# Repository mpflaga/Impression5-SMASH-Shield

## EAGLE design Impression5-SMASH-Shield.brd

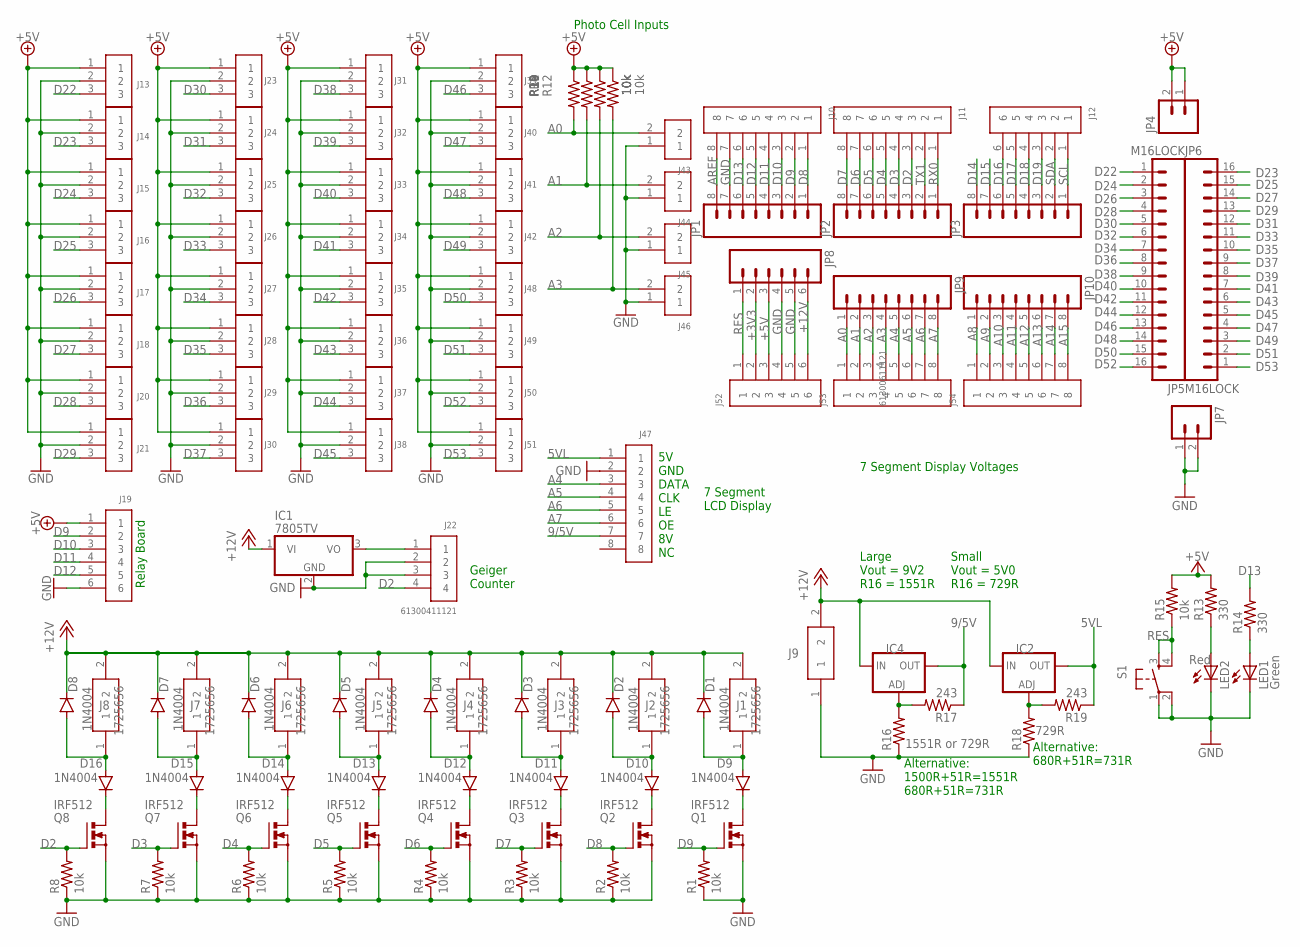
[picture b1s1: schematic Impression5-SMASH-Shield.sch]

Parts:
D1, D2, D3, D4, D5, D6, D7, D8, D9, D10, D11, D12, D13, D14, D15, D16: 1N4004; DO41-10
IC1: 7805TV; TO220V
IC2, IC4: LM317TS; 317TS
J1, J2, J3, J4, J5, J6, J7, J8, J9: 1725656
J10, J11, J47, J53, J54: 61300811121
J12, J19, J52: 61300611121
J13, J14, J15, J16, J17, J18, J20, J21, J23, J24, J25, J26, J27, J28, J29, J30, J31, J32, J33, J34, J35, J36, J37, J38, J39, J40, J41, J42, J48, J49, J50, J51: 61300311121
J22: 61300411121
J43, J44, J45, J46: 61300211121
JP1, JP2, JP3, JP9, JP10: M08LOCK; 1X08_LOCK
JP4, JP7: M02LOCK; 1X02_LOCK
JP5, JP6: M16LOCK; 1X16_LOCK
JP8: M06LOCK; 1X06_LOCK
LED1: Green; LED5MM
LED2: Red; LED5MM
Q1, Q2, Q3, Q4, Q5, Q6, Q7, Q8: IRF512; TO220BV
R1, R2, R3, R4, R5, R6, R7, R8, R9, R10, R11, R12, R15: 10k; AXIAL-0.3
R13, R14: 330; AXIAL-0.3
R16: 1551R or 729R; AXIAL-0.3
R17, R19: 243; AXIAL-0.3
R18: 729R; AXIAL-0.3
S1: TAC_SWITCHPTH; TACTILE-PTH

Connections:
5VG: IC1.3 (VO), J22.1
5VL: IC2.2 (OUT), J47.1, R19.P$1 (1)
9/5V: IC4.2 (OUT), J47.7, R17.P$1 (1)
+3V3: J52.2, JP8.2
+5V: J13.1, J14.1, J15.1, J16.1, J17.1, J18.1, J19.1, J20.1, J21.1, J23.1, J24.1, J25.1, J26.1, J27.1, J28.1, J29.1, J30.1, J31.1, J32.1, J33.1, J34.1, J35.1, J36.1, J37.1, J38.1, J39.1, J40.1, J41.1, J42.1, J48.1, J49.1, J50.1, J51.1, J52.3, JP4.1, JP4.2, JP8.3, R9.P$1 (1), R10.P$1 (1), R11.P$1 (1), R12.P$1 (1), R13.P$2 (2), R15.P$2 (2)
+12V: D1.C, D2.C, D3.C, D4.C, D5.C, D6.C, D7.C, D8.C, IC1.1 (VI), IC2.3 (IN), IC4.3 (IN), J1.2, J2.2, J3.2, J4.2, J5.2, J6.2, J7.2, J8.2, J9.2, J52.6, JP8.6
A0: J43.2, J53.1, JP9.1, R9.P$2 (2)
A1: J44.2, J53.2, JP9.2, R10.P$2 (2)
A2: J45.2, J53.3, JP9.3, R11.P$2 (2)
A3: J46.2, J53.4, JP9.4, R12.P$2 (2)
A4: J47.3, J53.5, JP9.5
A5: J47.4, J53.6, JP9.6
A6: J47.5, J53.7, JP9.7
A7: J47.6, J53.8, JP9.8
A8: J54.1, JP10.1
A9: J54.2, JP10.2
A10: J54.3, JP10.3
A11: J54.4, JP10.4
A12: J54.5, JP10.5
A13: J54.6, JP10.6
A14: J54.7, JP10.7
A15: J54.8, JP10.8
AREF: J10.8, JP1.8
D2: J11.3, J22.4, JP2.3, Q8.G, R8.P$2 (2)
D3: J11.4, JP2.4, Q7.G, R7.P$2 (2)
D4: J11.5, JP2.5, Q6.G, R6.P$2 (2)
D5: J11.6, JP2.6, Q5.G, R5.P$2 (2)
D6: J11.7, JP2.7, Q4.G, R4.P$2 (2)
D7: J11.8, JP2.8, Q3.G, R3.P$2 (2)
D8: J10.1, JP1.1, Q2.G, R2.P$2 (2)
D9: J10.2, J19.2, JP1.2, Q1.G, R1.P$2 (2)
D10: J10.3, J19.3, JP1.3
D11: J10.4, J19.4, JP1.4
D12: J10.5, J19.5, JP1.5
D13: J10.6, JP1.6, R14.P$2 (2)
D14: JP3.8
D15: JP3.7
D16: J12.6, JP3.6
D17: J12.5, JP3.5
D18: J12.4, JP3.4
D19: J12.3, JP3.3
D22: J13.3, JP5.1
D23: J14.3, JP6.16
D24: J15.3, JP5.2
D25: J16.3, JP6.15
D26: J17.3, JP5.3
D27: J18.3, JP6.14
D28: J20.3, JP5.4
D29: J21.3, JP6.13
D30: J23.3, JP5.5
D31: J24.3, JP6.12
D32: J25.3, JP5.6
D33: J26.3, JP6.11
D34: J27.3, JP5.7
D35: J28.3, JP6.10
D36: J29.3, JP5.8
D37: J30.3, JP6.9
D38: J31.3, JP5.9
D39: J32.3, JP6.8
D40: J33.3, JP5.10
D41: J34.3, JP6.7
D42: J35.3, JP5.11
D43: J36.3, JP6.6
D44: J37.3, JP5.12
D45: J38.3, JP6.5
D46: J39.3, JP5.13
D47: J40.3, JP6.4
D48: J41.3, JP5.14
D49: J42.3, JP6.3
D50: J48.3, JP5.15
D51: J49.3, JP6.2
D52: J50.3, JP5.16
D53: J51.3, JP6.1
GND: IC1.2 (GND), J9.1, J10.7, J13.2, J14.2, J15.2, J16.2, J17.2, J18.2, J19.6, J20.2, J21.2, J22.2, J22.3, J23.2, J24.2, J25.2, J26.2, J27.2, J28.2, J29.2, J30.2, J31.2, J32.2, J33.2, J34.2, J35.2, J36.2, J37.2, J38.2, J39.2, J40.2, J41.2, J42.2, J43.1, J44.1, J45.1, J46.1, J47.2, J48.2, J49.2, J50.2, J51.2, J52.4, J52.5, JP1.7, JP7.1, JP7.2, JP8.4, JP8.5, LED1.K (C), LED2.K (C), Q1.S, Q2.S, Q3.S, Q4.S, Q5.S, Q6.S, Q7.S, Q8.S, R1.P$1 (1), R2.P$1 (1), R3.P$1 (1), R4.P$1 (1), R5.P$1 (1), R6.P$1 (1), R7.P$1 (1), R8.P$1 (1), R16.P$1 (1), R18.P$1 (1), S1.1, S1.2
unnamed: D8.A, D16.A, J8.1
unnamed: D16.C, Q8.D
unnamed: D7.A, D15.A, J7.1
unnamed: D15.C, Q7.D
unnamed: D6.A, D14.A, J6.1
unnamed: D14.C, Q6.D
unnamed: D5.A, D13.A, J5.1
unnamed: D13.C, Q5.D
unnamed: D4.A, D12.A, J4.1
unnamed: D12.C, Q4.D
unnamed: D3.A, D11.A, J3.1
unnamed: D11.C, Q3.D
unnamed: D2.A, D10.A, J2.1
unnamed: D10.C, Q2.D
unnamed: D1.A, D9.A, J1.1
unnamed: D9.C, Q1.D
unnamed: IC4.1 (ADJ), R16.P$2 (2), R17.P$2 (2)
unnamed: IC2.1 (ADJ), R18.P$2 (2), R19.P$2 (2)
unnamed: LED2.A, R13.P$1 (1)
unnamed: LED1.A, R14.P$1 (1)
RES: J52.1, JP8.1, R15.P$1 (1), S1.3, S1.4
RX0: J11.1, JP2.1
SCL: J12.1, JP3.1
SDA: J12.2, JP3.2
TX1: J11.2, JP2.2

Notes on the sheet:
Relay Board
Photo Cell Inputs
5V GND DATA CLK LE OE 8V NC
7 Segment LCD Display
Geiger Counter
7 Segment Display Voltages
Large Vout = 9V2 R16 = 1551R
Small Vout = 5V0 R16 = 729R
Alternative: 680R+51R=731R
Alternative: 1500R+51R=1551R 680R+51R=731R

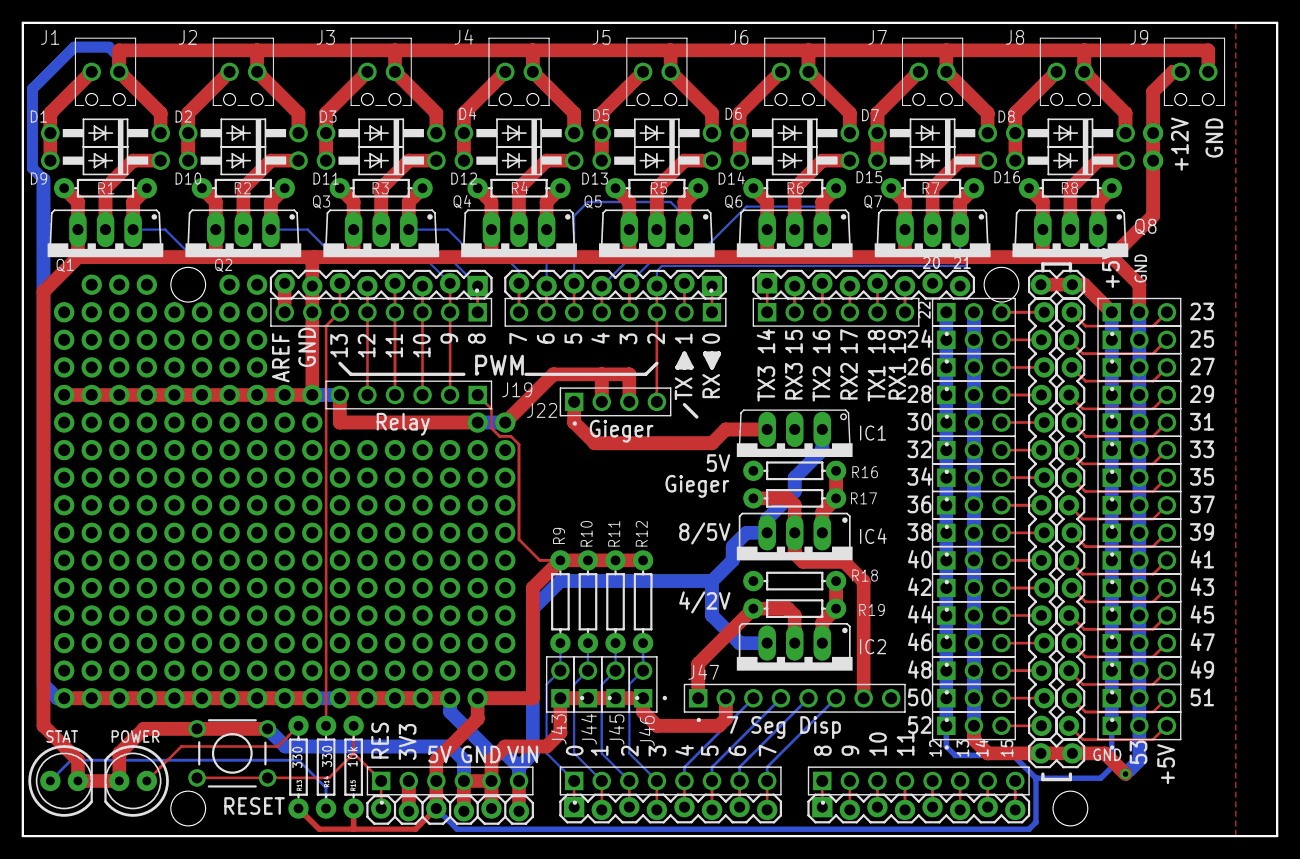
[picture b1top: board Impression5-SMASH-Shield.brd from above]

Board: 2 copper layers, 115.6 x 74.9 mm, 113 parts (0 on the bottom side), 97 nets.

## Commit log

2019-08-04 Changed the Order of the Text to better line up the LM317 Programming Resistors.
2019-08-04 changed 4/2V to 5VL. This powers the VDD of the TLC5917 and needs to be 5V.
2019-08-04 Changed the 8/5V to 9/5V, actually 9V2 and 5V0 respectively. These voltages needs to provide the maximum Vf that the 7-Segments may need. The max Vf are: SA23-11SRWA = 9.2V SA15-11EWA = 5.0V
2019-08-04 updated PDF to match recent changes in LM317 programming voltages.
2019-08-04 Added Notes for double use of D2 and D9
